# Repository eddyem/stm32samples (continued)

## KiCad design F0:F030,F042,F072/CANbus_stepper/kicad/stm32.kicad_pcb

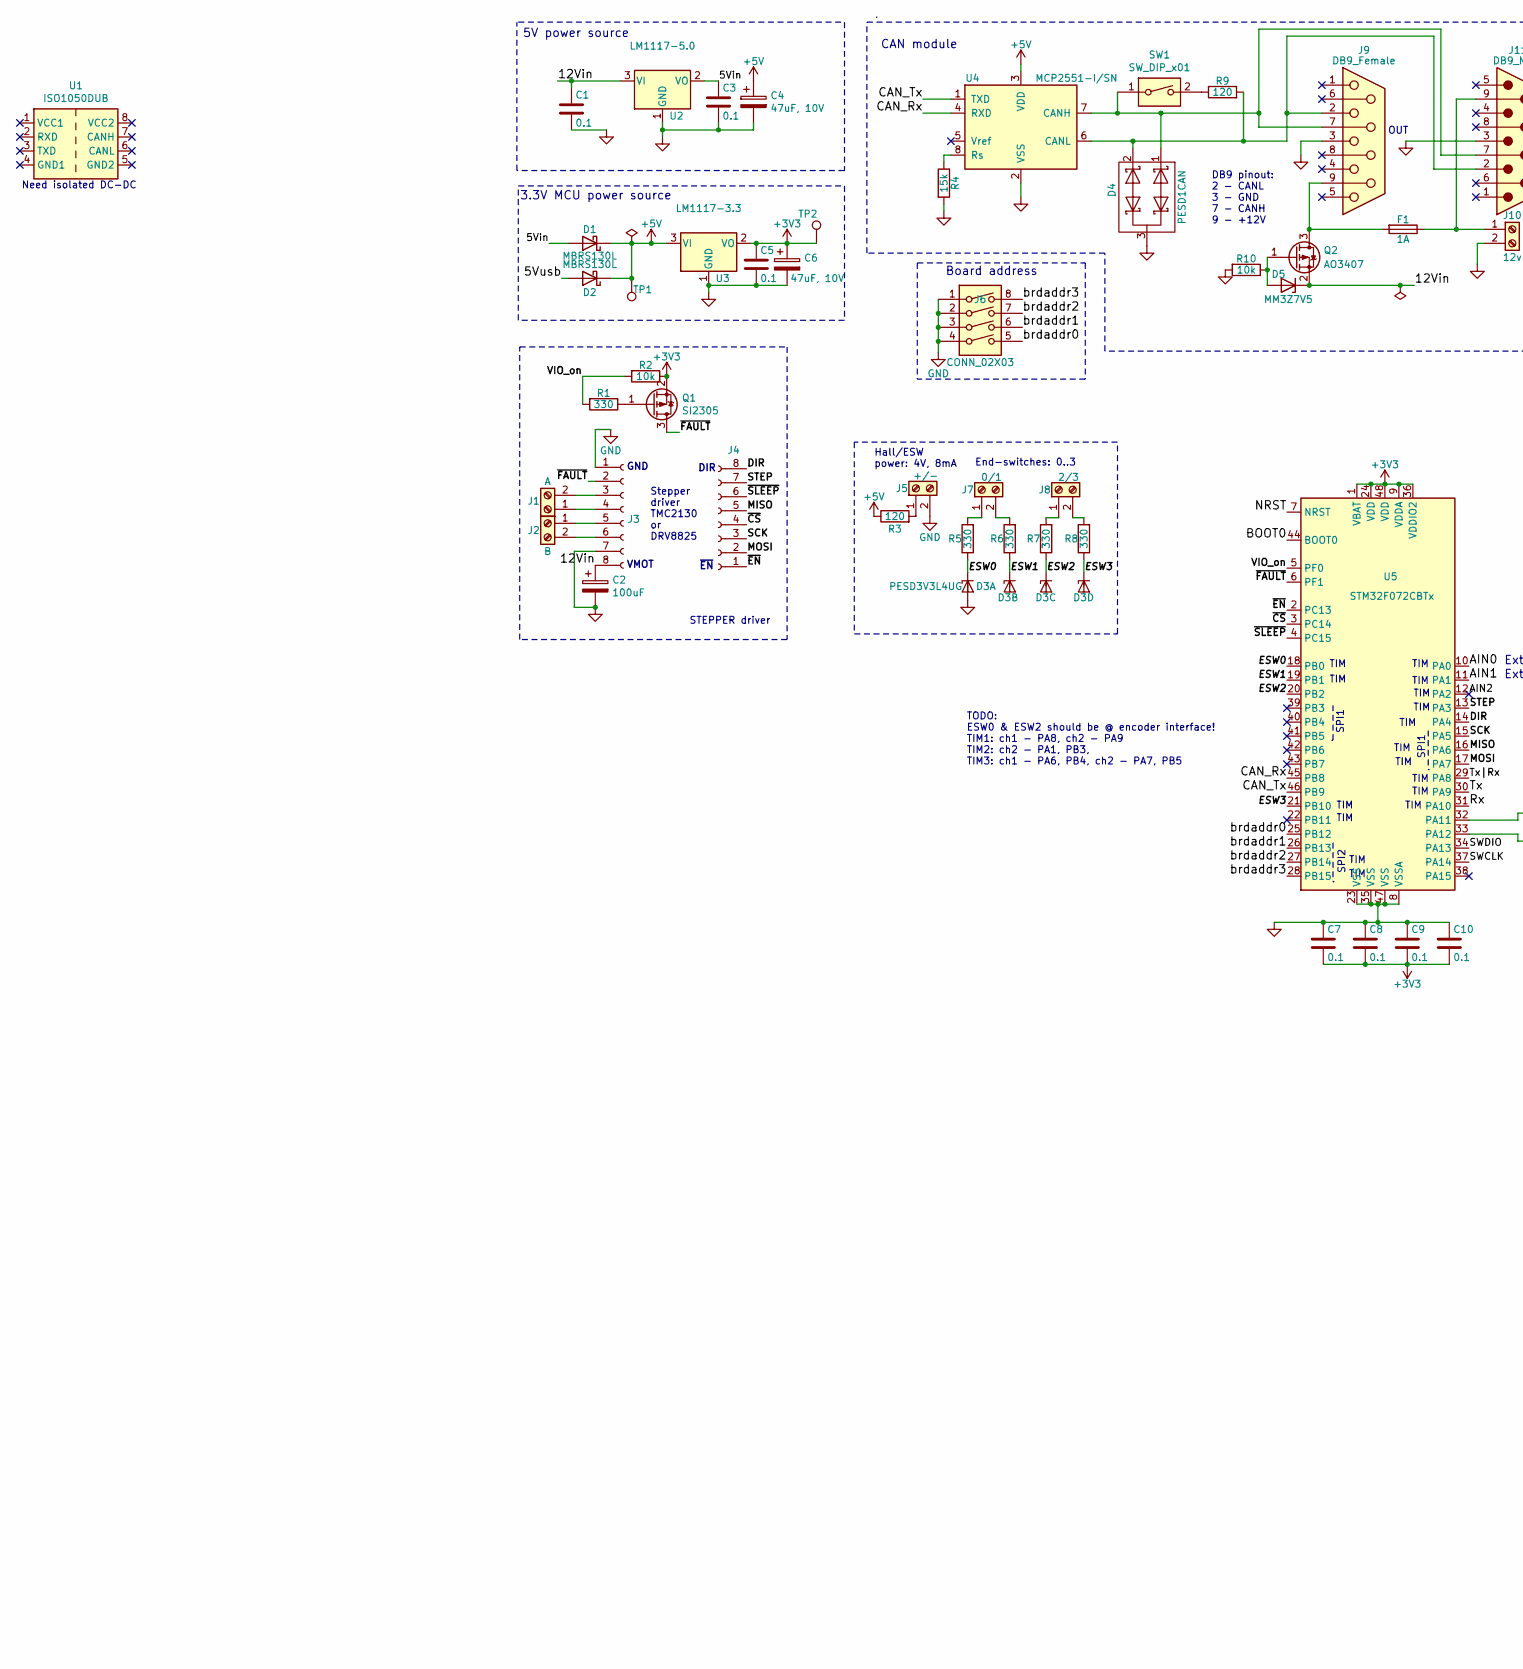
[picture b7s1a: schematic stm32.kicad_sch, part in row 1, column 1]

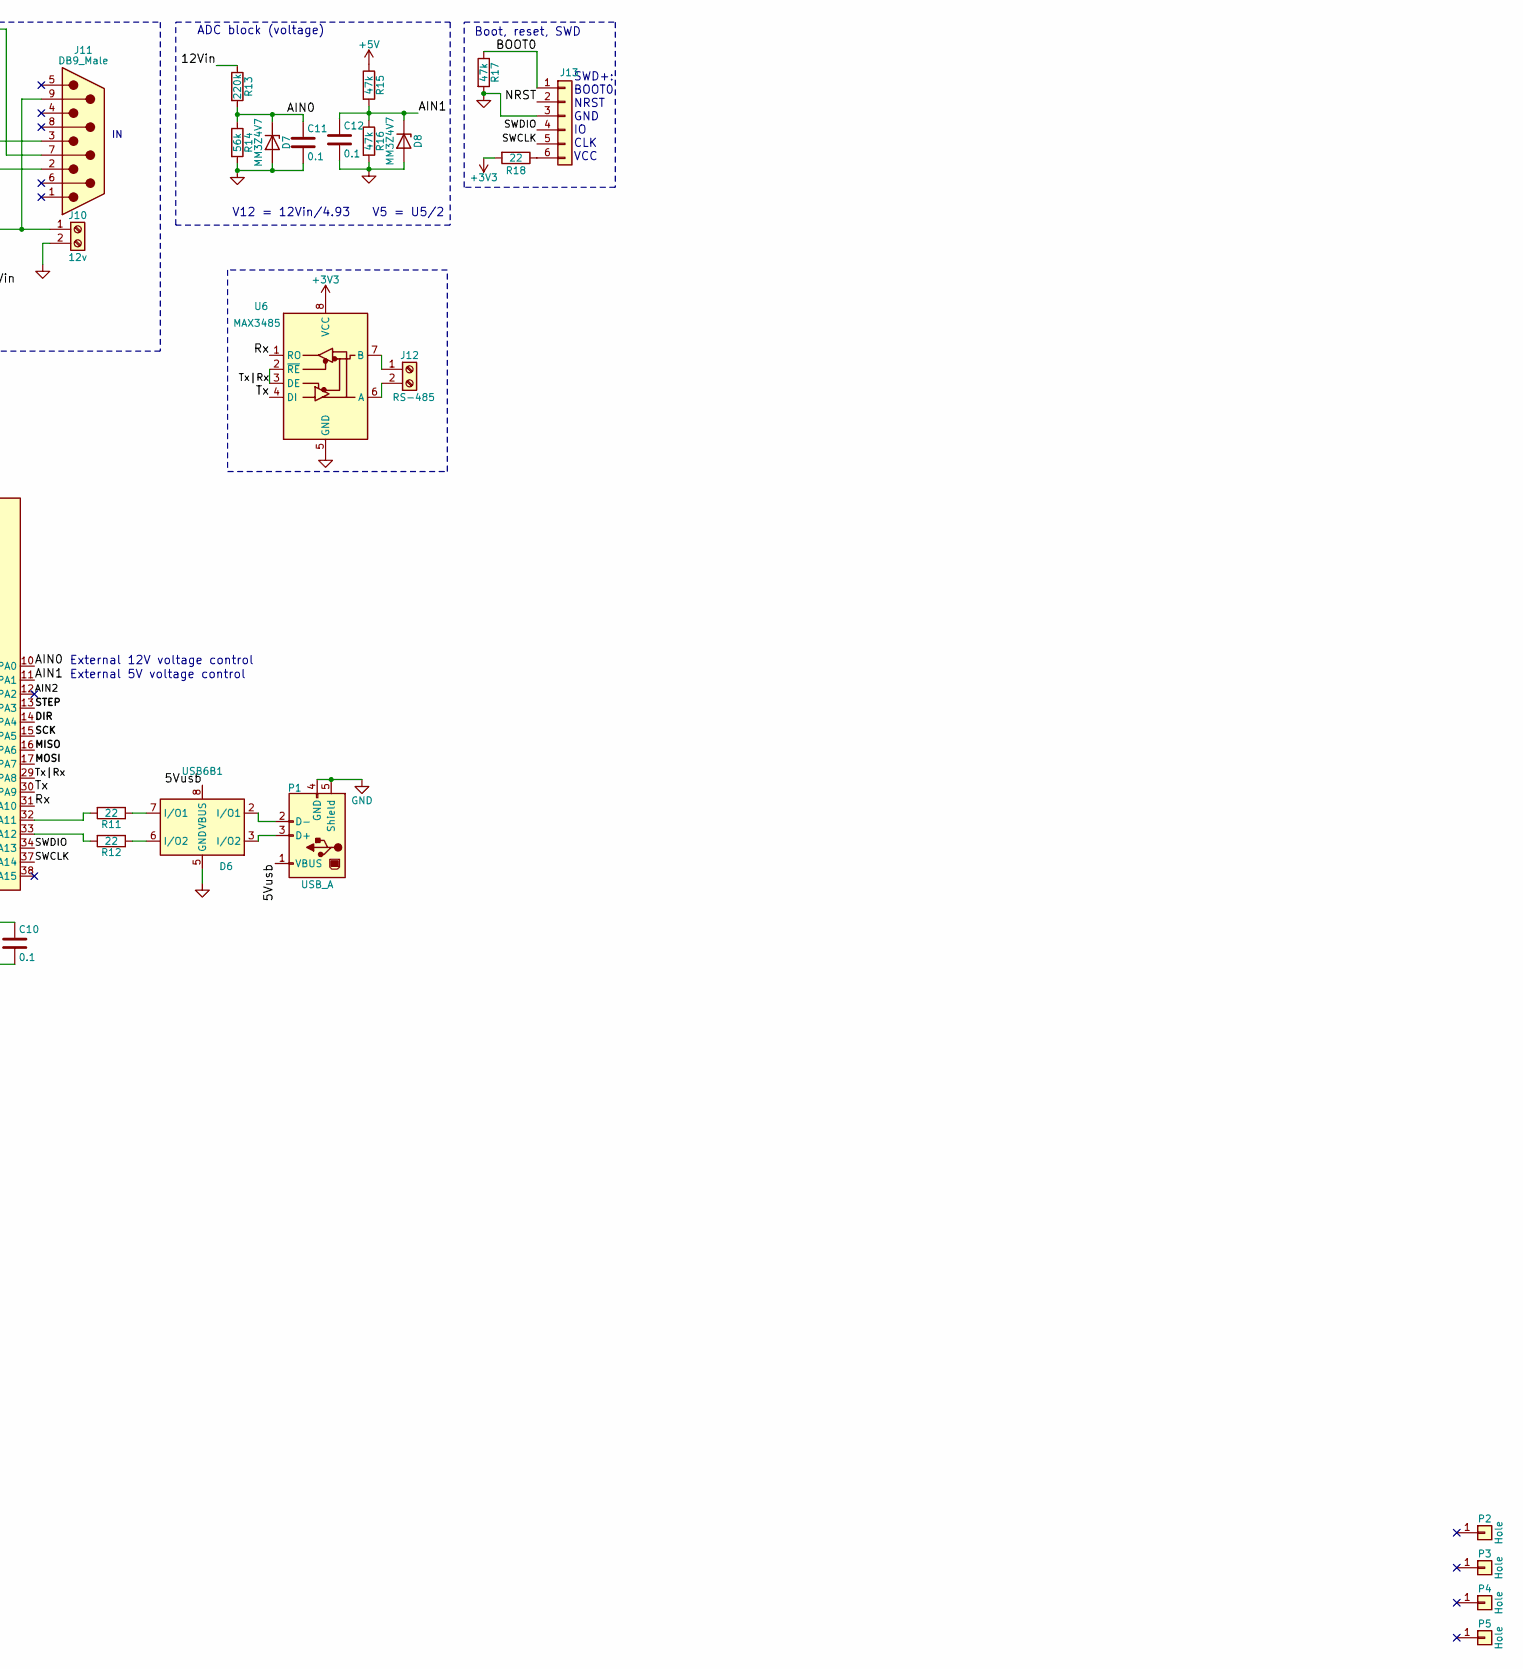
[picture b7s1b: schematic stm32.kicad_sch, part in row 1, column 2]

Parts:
C1, C3, C5, C7, C8, C9, C10, C11, C12: 0.1; C_0603_1608Metric_Pad1.05x0.95mm_HandSolder
C2: 100uF; CP_Radial_D8.0mm_P3.50mm
C4, C6: 47uF, 10V; CP_EIA-6032-28_Kemet-C_Pad2.25x2.35mm_HandSolder
D1, D2: MBRS130L; D_SMB_Handsoldering
D3: PESD3V3L4UG; SOT-363_SC-70-6_Handsoldering
D4: PESD1CAN; SOT-23_Handsoldering
D5: MM3Z7V5; D_0805_2012Metric_Pad1.15x1.40mm_HandSolder
D6: USB6B1; SOIC-8_3.9x4.9mm_P1.27mm
D7, D8: MM3Z4V7; D_0805_2012Metric_Pad1.15x1.40mm_HandSolder
F1: 1A; FuseHolder
J1: A; TerminalBlock_Phoenix_MKDS-1,5-2_1x02_P5.00mm_Horizontal
J2: B; TerminalBlock_Phoenix_MKDS-1,5-2_1x02_P5.00mm_Horizontal
J3, J4: Conn_01x08_Female; PinSocket_1x08_P2.54mm_Vertical
J5: +/-; TerminalBlock_Phoenix_MKDS-1,5-2_1x02_P5.00mm_Horizontal
J6: CONN_02X03; SW_DIP_SPSTx04_Slide_9.78x12.34mm_W7.62mm_P2.54mm
J7: 0/1; TerminalBlock_Phoenix_MKDS-1,5-2_1x02_P5.00mm_Horizontal
J8: 2/3; TerminalBlock_Phoenix_MKDS-1,5-2_1x02_P5.00mm_Horizontal
J9: DB9_Female; DSUB-9_Female_Horizontal_P2.77x2.84mm_EdgePinOffset4.94mm_H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
J10: 12v; TerminalBlock_Phoenix_MKDS-1,5-2_1x02_P5.00mm_Horizontal
J11: DB9_Male; DSUB-9_Male_Horizontal_P2.77x2.84mm_EdgePinOffset4.94mm_Hou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
J12: RS-485; TerminalBlock_Phoenix_MKDS-1,5-2_1x02_P5.00mm_Horizontal
J13: Conn_01x06; PinSocket_1x06_P2.54mm_Vertical
P1: USB_A; USB_B_OST_USB-B1HSxx_Horizontal
P2, P3, P4, P5: Hole; MountingHole_3.2mm_M3
Q1: SI2305; SOT-23_Handsoldering
Q2: AO3407; SOT-23_Handsoldering
R1, R5, R6, R7, R8: 330; R_0603_1608Metric_Pad1.05x0.95mm_HandSolder
R2, R10: 10k; R_0603_1608Metric_Pad1.05x0.95mm_HandSolder
R3, R9: 120; R_0603_1608Metric_Pad1.05x0.95mm_HandSolder
R4: 15k; R_0603_1608Metric_Pad1.05x0.95mm_HandSolder
R11, R12, R18: 22; R_0603_1608Metric_Pad1.05x0.95mm_HandSolder
R13: 220k; R_0603_1608Metric_Pad1.05x0.95mm_HandSolder
R14: 56k; R_0603_1608Metric_Pad1.05x0.95mm_HandSolder
R15, R16, R17: 47k; R_0603_1608Metric_Pad1.05x0.95mm_HandSolder
SW1: SW_DIP_x01; SW_DIP_SPSTx01_Slide_6.7x4.1mm_W7.62mm_P2.54mm_LowProfile
TP1, TP2: TestPoint; PinHeader_1x01_P2.54mm_Vertical
U1: ISO1050DUB; SOP-8_6.62x9.15mm_P2.54mm
U2: LM1117-5.0; SOT-223-3_TabPin2
U3: LM1117-3.3; SOT-223-3_TabPin2
U4: MCP2551-I/SN; SOIC-8_3.9x4.9mm_P1.27mm
U5: STM32F072CBTx; LQFP-48_7x7mm_P0.5mm
U6: MAX3485; SO-8_3.9x4.9mm_P1.27mm

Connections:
+3V3: C5.1, C6.1, C7.2, C8.2, C9.2, C10.2, Q1.2 (S), R2.1, R18.2, TP2.1, U3.2 (VO), U5.1 (VBAT), U5.9 (VDDA), U5.24 (VDD), U5.36 (VDDIO2), U5.48 (VDD), U6.8 (VCC)
+5V: C4.1, D1.1 (K), D2.1 (K), R3.1, R15.1, TP1.1, U3.3 (VI), U4.3 (VDD)
/5Vin: C3.1, D1.2 (A), U2.2 (VO)
/5Vusb: D2.2 (A), D6.1 (VBUS), D6.8 (VBUS), P1.1 (VBUS)
/12Vin: C1.1, C2.1, D5.1 (K), J3.8, Q2.2 (S), R13.1, U2.3 (VI)
/AIN0: C11.1, D7.1 (K), R13.2, R14.1, U5.10 (PA0)
/AIN1: C12.1, D8.1 (K), R15.2, R16.1, U5.11 (PA1)
/BOOT0: J13.1, R17.1, U5.44 (BOOT0)
/CAN_Rx: U4.4 (RXD), U5.45 (PB8)
/CAN_Tx: U4.1 (TXD), U5.46 (PB9)
/DIR: J4.8, U5.14 (PA4)
/ESW0: D3.1 (K1), R5.1, U5.18 (PB0)
/ESW1: D3.3 (K2), R6.1, U5.19 (PB1)
/ESW2: D3.4 (K3), R7.1, U5.20 (PB2)
/ESW3: D3.6 (K4), R8.1, U5.21 (PB10)
/MISO: J4.5, U5.16 (PA6)
/MOSI: J4.2, U5.17 (PA7)
/NRST: J13.2, U5.7 (NRST)
/Rx: U5.31 (PA10), U6.1 (RO)
/SCK: J4.3, U5.15 (PA5)
/STEP: J4.7, U5.13 (PA3)
/SWCLK: J13.5, U5.37 (PA14)
/SWDIO: J13.4, U5.34 (PA13)
/Tx: U5.30 (PA9), U6.4 (DI)
/Tx|Rx: U5.29 (PA8), U6.2 (~RE), U6.3 (DE)
/VIO_on: R1.2, R2.2, U5.5 (PF0)
/brdaddr0: J6.5, U5.25 (PB12)
/brdaddr1: J6.6, U5.26 (PB13)
/brdaddr2: J6.7, U5.27 (PB14)
/brdaddr3: J6.8, U5.28 (PB15)
/~CS: J4.4, U5.3 (PC14)
/~EN: J4.1, U5.2 (PC13)
/~FAULT: J3.2, Q1.3 (D), U5.6 (PF1)
/~SLEEP: J4.6, U5.4 (PC15)
GND: C1.2, C2.2, C3.2, C4.2, C5.2, C6.2, C7.1, C8.1, C9.1, C10.1, C11.2, C12.2, D3.2 (A), D4.3 (O), D6.4 (GND), D6.5 (GND), D7.2 (A), D8.2 (A), J3.1, J3.7, J5.2, J6.1, J6.2, J6.3, J6.4, J9.3, J10.2, J11.3, J13.3, P1.4 (GND), P1.5 (Shield), R4.2, R10.2, R14.2, R16.2, R17.2, U2.1 (GND), U3.1 (GND), U4.2 (VSS), U5.8 (VSSA), U5.23 (VSS), U5.35 (VSS), U5.47 (VSS), U6.5 (GND)
unnamed: D4.1 (K), J9.7, J11.7, SW1.1, U4.7 (CANH)
unnamed: D4.2 (K), J9.2, J11.2, R9.2, U4.6 (CANL)
unnamed: D5.2 (A), Q2.1 (G), R10.1
unnamed: D6.2 (I/O1), P1.2 (D-)
unnamed: D6.3 (I/O2), P1.3 (D+)
unnamed: D6.6 (I/O2), R12.1
unnamed: D6.7 (I/O1), R11.1
unnamed: F1.1, J10.1, J11.9
unnamed: F1.2, J9.9, Q2.3 (D)
unnamed: J1.1, J3.4
unnamed: J1.2, J3.3
unnamed: J2.1, J3.5
unnamed: J2.2, J3.6
unnamed: J5.1, R3.2
unnamed: J7.1, R5.2
unnamed: J7.2, R6.2
unnamed: J8.1, R7.2
unnamed: J8.2, R8.2
unnamed: J12.1, U6.7 (B)
unnamed: J12.2, U6.6 (A)
unnamed: J13.6, R18.1
unnamed: Q1.1 (G), R1.1
unnamed: R4.1, U4.8 (Rs)
unnamed: R9.1, SW1.2
unnamed: R11.2, U5.32 (PA11)
unnamed: R12.2, U5.33 (PA12)

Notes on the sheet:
TIM
Hall/ESW power: 4V, 8mA
CAN module
End-switches: 0..3
5V power source
Need isolated DC-DC
OUT
GND
External 5V voltage control
Boot, reset, SWD
SPI2
Board address
Stepper driver TMC2130 or DRV8825
ADC block (voltage)
DIR
SPI1
~{EN}
STEPPER driver
V12 = 12Vin/4.93
DB9 pinout: 2 - CANL 3 - GND 7 - CANH 9 - +12V
TODO: ESW0 & ESW2 should be @ encoder interface! TIM1: ch1 - PA8, ch2 - PA9 TIM2: ch2 - PA1, PB3, TIM3: ch1 - PA6, PB4, ch2 - PA7, PB5
External 12V voltage control
V5 = U5/2
3.3V MCU power source
SWD+: BOOT0 NRST GND IO CLK VCC
VMOT

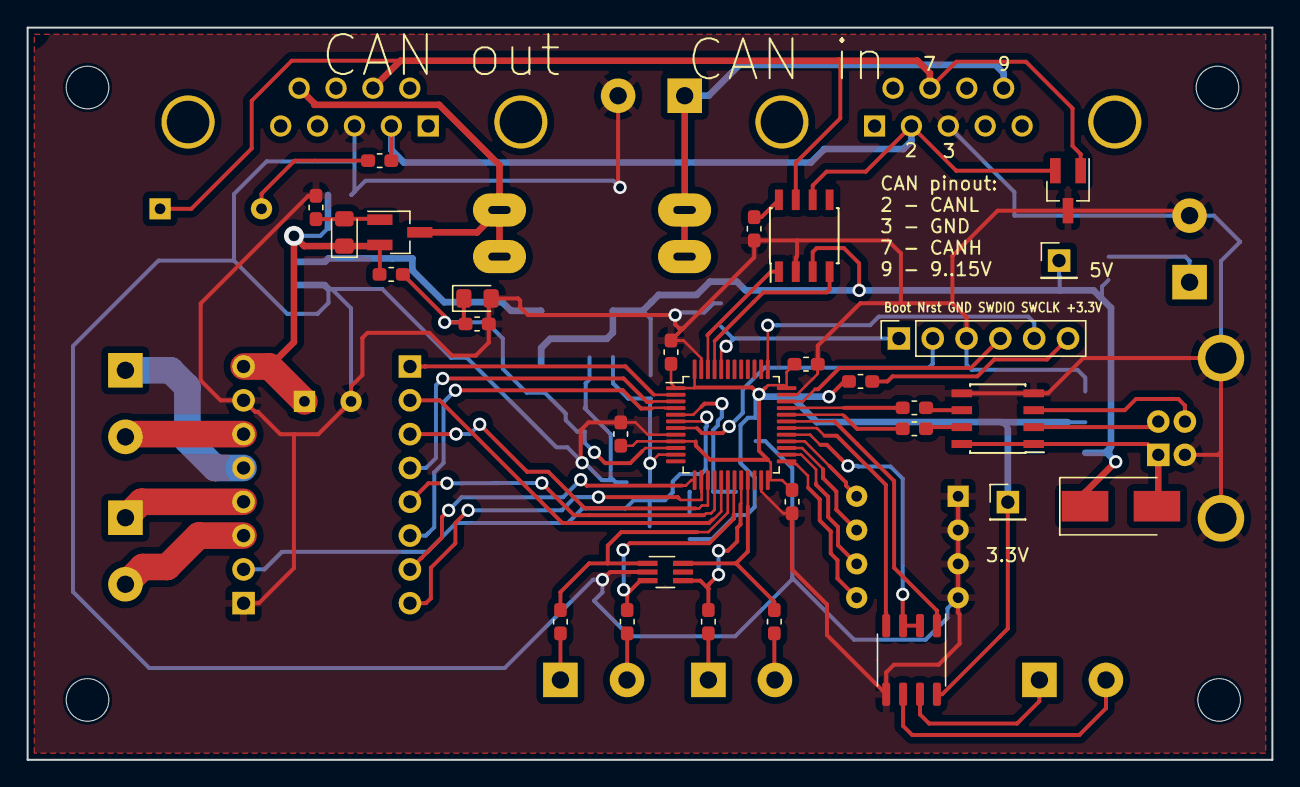
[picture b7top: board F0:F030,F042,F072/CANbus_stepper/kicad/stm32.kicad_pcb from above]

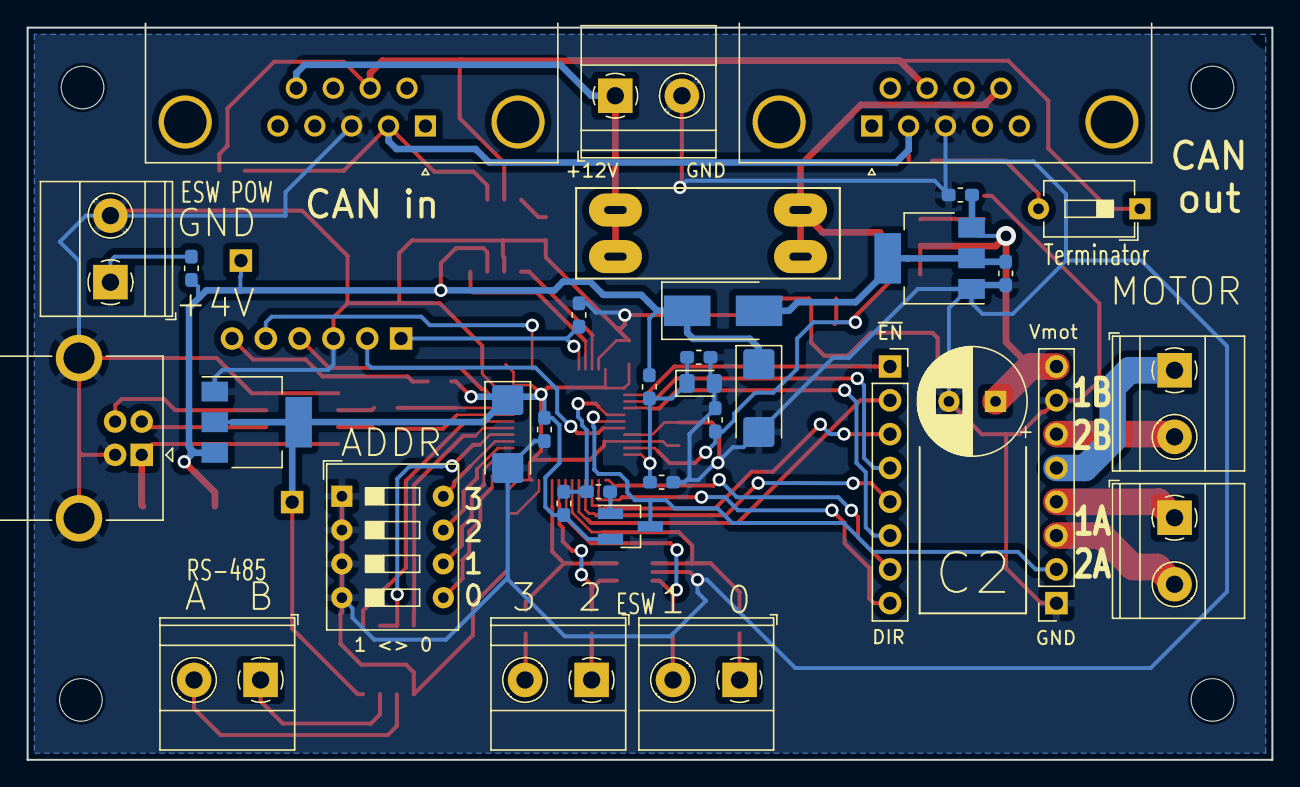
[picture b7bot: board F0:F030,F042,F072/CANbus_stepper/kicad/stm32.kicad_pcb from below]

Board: 2 copper layers, 93.5 x 55.0 mm, 67 parts (34 on the bottom side), 61 nets.
